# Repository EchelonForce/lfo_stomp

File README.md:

# Eurorack LFO Stomp

This is a PCB for a eurorack LFO based on the STOMPLFO chip from Electric Druid.

Full writeup here: https://www.robotdialogs.com/2022/09/eurorack-lfo-module-stomp-lfo.html

This work is licensed under a Creative Commons Attribution-NonCommercial-ShareAlike 4.0 International License. https://creativecommons.org/licenses/by-nc-sa/4.0/

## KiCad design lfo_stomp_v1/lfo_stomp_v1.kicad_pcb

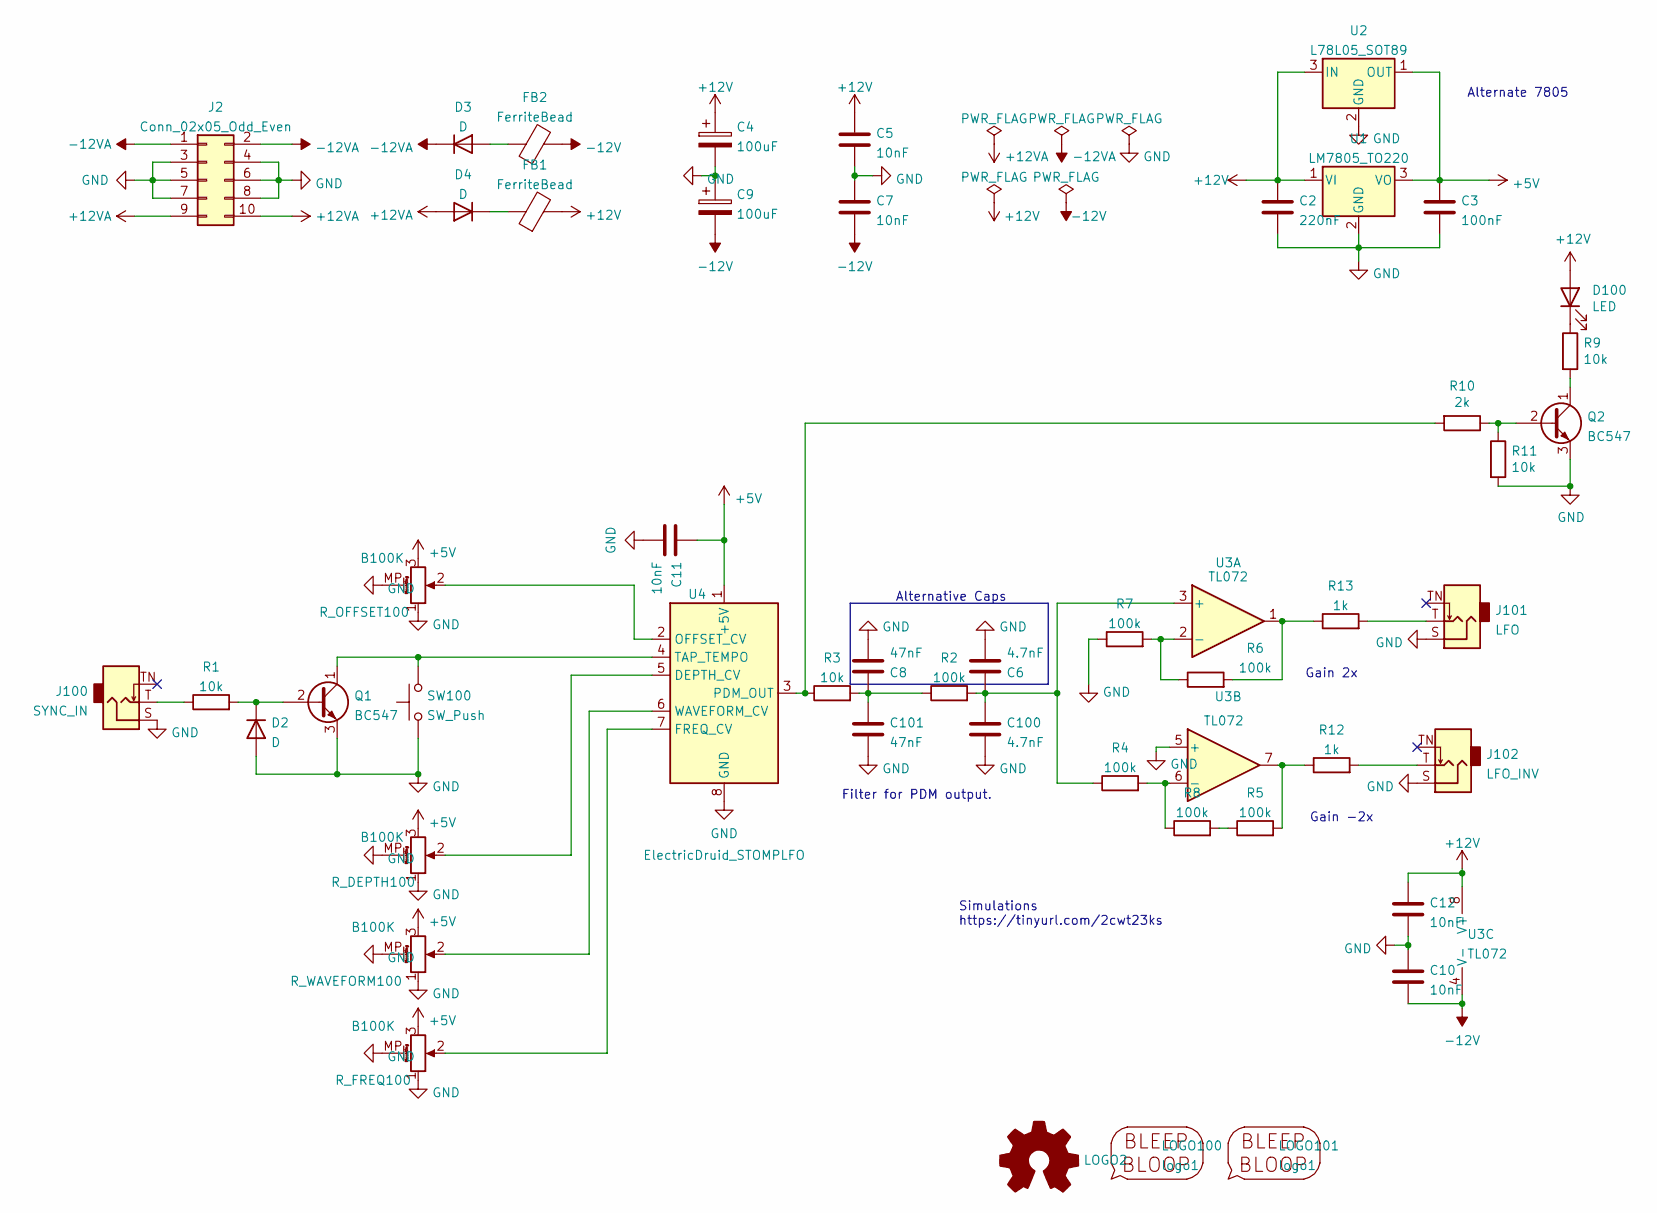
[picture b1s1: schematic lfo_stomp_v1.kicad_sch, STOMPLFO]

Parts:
C2: 220nF; C_1206_3216Metric_Pad1.33x1.80mm_HandSolder
C3: 100nF; C_1206_3216Metric_Pad1.33x1.80mm_HandSolder
C4, C9: 100uF; CP_Radial_D5.0mm_P2.50mm
C5, C7, C10, C11, C12: 10nF; C_1206_3216Metric_Pad1.33x1.80mm_HandSolder
C6: 4.7nF; C_1206_3216Metric_Pad1.33x1.80mm_HandSolder
C8: 47nF; C_1206_3216Metric_Pad1.33x1.80mm_HandSolder
C100: 4.7nF; C_Disc_D5.1mm_W3.2mm_P5.00mm
C101: 47nF; C_Disc_D5.1mm_W3.2mm_P5.00mm
D2, D3, D4: D; D_A-405_P7.62mm_Horizontal
D100: LED; LED_D3.0mm
FB1, FB2: FerriteBead; L_Axial_L5.3mm_D2.2mm_P2.54mm_Vertical_Vishay_IM-1
J2: Conn_02x05_Odd_Even; IDC-Header_2x05_P2.54mm_Vertical
J100: SYNC_IN; Jack_3.5mm_MJ-355W_and_PJ398SM_Vertical
J101: LFO; Jack_3.5mm_MJ-355W_and_PJ398SM_Vertical
J102: LFO_INV; Jack_3.5mm_MJ-355W_and_PJ398SM_Vertical
LOGO2: Logo_Open_Hardware_Small; OSHW-Symbol_6.7x6mm_SilkScreen
LOGO100: logo1; Logo1
LOGO101: logo1; Logo2
Q1, Q2: BC547; TO-92_Inline_Wide
R1, R3, R9, R11: 10k; R_1206_3216Metric_Pad1.30x1.75mm_HandSolder
R2, R4, R5, R6, R7, R8: 100k; R_1206_3216Metric_Pad1.30x1.75mm_HandSolder
R10: 2k; R_1206_3216Metric_Pad1.30x1.75mm_HandSolder
R12, R13: 1k; R_1206_3216Metric_Pad1.30x1.75mm_HandSolder
R_DEPTH100: B100K; Potentiometer_Alpha_RD901F-40-00D_Single_Vertical_w_3d
R_FREQ100: B100K; Potentiometer_Alpha_RD901F-40-00D_Single_Vertical_w_3d
R_OFFSET100: B100K; Potentiometer_Alpha_RD901F-40-00D_Single_Vertical_w_3d
R_WAVEFORM100: B100K; Potentiometer_Alpha_RD901F-40-00D_Single_Vertical_w_3d
SW100: SW_Push; SW_PS1024ALRED
U1: LM7805_TO220; TO-220-3_Vertical
U2: L78L05_SOT89; SOT-89-3
U3: TL072; DIP-8_W7.62mm_Socket_LongPads
U4: ElectricDruid_STOMPLFO; DIP-8_W7.62mm_Socket_LongPads

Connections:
+5V: C3.1, C11.1, R_DEPTH100.3, R_FREQ100.3, R_OFFSET100.3, R_WAVEFORM100.3, U1.3 (VO), U2.1 (OUT), U4.1 (+5V)
+12V: C2.1, C4.1, C5.1, C12.1, D100.2 (A), FB1.2, U1.1 (VI), U2.3 (IN), U3.8 (V+)
+12VA: D4.2 (A), J2.9, J2.10
-12V: C7.2, C9.2, C10.2, FB2.2, U3.4 (V-)
-12VA: D3.1 (K), J2.1, J2.2
GND: C2.2, C3.2, C4.2, C5.2, C6.2, C7.1, C8.2, C9.1, C10.1, C11.2, C12.2, C100.2, C101.2, D2.2 (A), J2.3, J2.4, J2.5, J2.6, J2.7, J2.8, J100.S, J101.S, J102.S, Q1.3 (E), Q2.3 (E), R7.1, R11.2, R_DEPTH100.1, R_DEPTH100.MP (MountPin), R_FREQ100.1, R_FREQ100.MP (MountPin), R_OFFSET100.1, R_OFFSET100.MP (MountPin), R_WAVEFORM100.1, R_WAVEFORM100.MP (MountPin), SW100.1, U1.2 (GND), U2.2 (GND), U3.5 (+), U4.8 (GND)
unnamed: C6.1, C100.1, R2.2, R4.1, U3.3 (+)
unnamed: C8.1, C101.1, R2.1, R3.2
unnamed: D2.1 (K), Q1.2 (B), R1.2
unnamed: D3.2 (A), FB2.1
unnamed: D4.1 (K), FB1.1
unnamed: D100.1 (K), R9.1
unnamed: J100.T, R1.1
unnamed: J101.T, R13.2
unnamed: J102.T, R12.2
unnamed: Q1.1 (C), SW100.2, U4.4 (TAP_TEMPO)
unnamed: R3.1, R10.2, U4.3 (PDM_OUT)
unnamed: R4.2, R8.1, U3.6 (-)
unnamed: R5.1, R8.2
unnamed: R6.1, R7.2, U3.2 (-)
unnamed: Q2.1 (C), R9.2
unnamed: Q2.2 (B), R10.1, R11.1
unnamed: R5.2, R12.1, U3.7
unnamed: R6.2, R13.1, U3.1
unnamed: R_DEPTH100.2, U4.5 (DEPTH_CV)
unnamed: R_FREQ100.2, U4.7 (FREQ_CV)
unnamed: R_OFFSET100.2, U4.2 (OFFSET_CV)
unnamed: R_WAVEFORM100.2, U4.6 (WAVEFORM_CV)

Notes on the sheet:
Filter for PDM output.
Gain 2x
Gain -2x
Simulations https://tinyurl.com/2cwt23ks
Alternate 7805
Alternative Caps

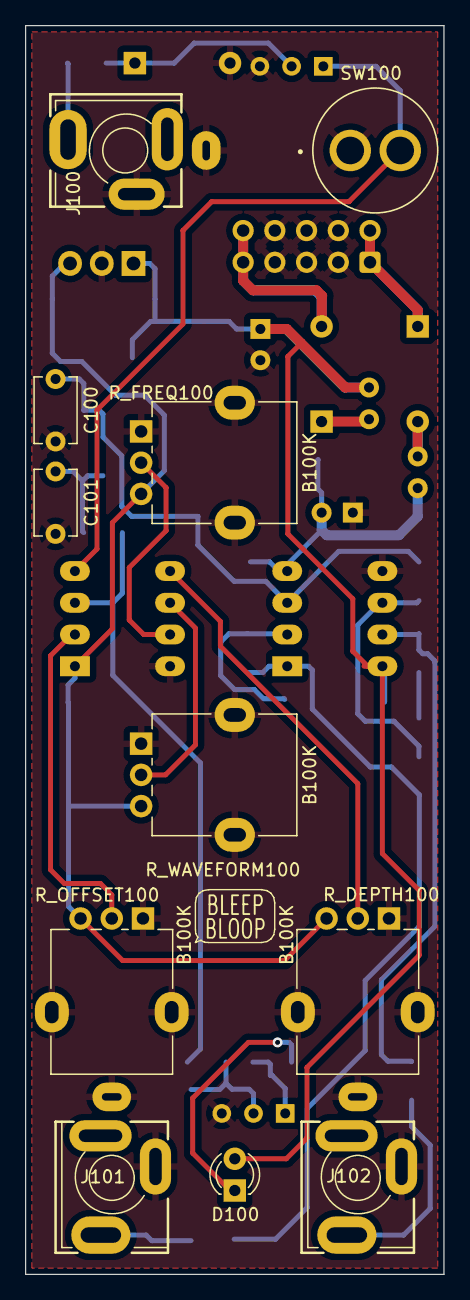
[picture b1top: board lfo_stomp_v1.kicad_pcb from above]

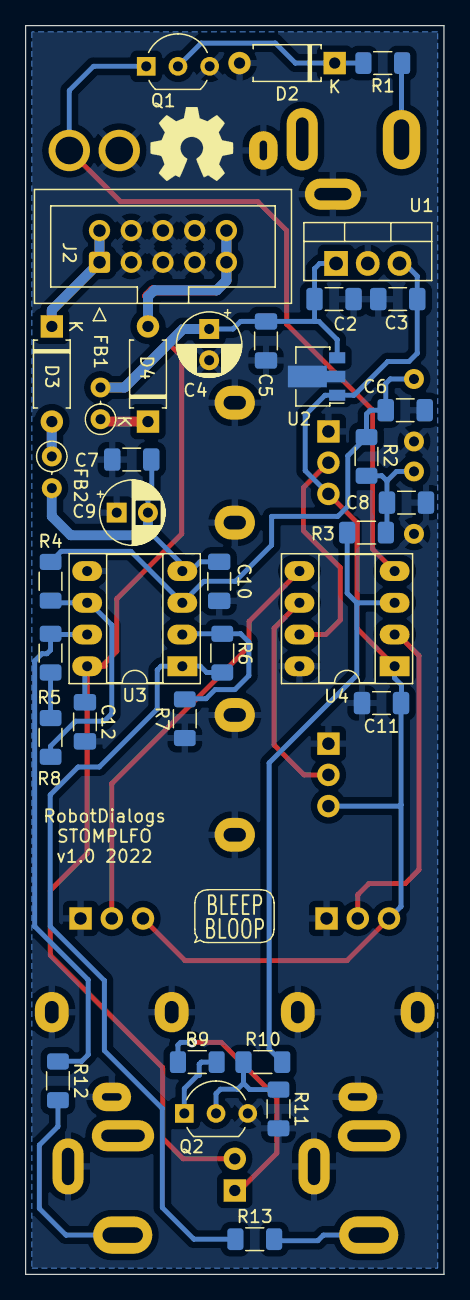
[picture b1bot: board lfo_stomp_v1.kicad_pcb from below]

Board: 2 copper layers, 33.5 x 100.0 mm, 50 parts (37 on the bottom side), 28 nets.

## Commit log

2022-06-25 Initial commit with .gitignore
2022-06-25 v1 before renaming references
2022-06-25 Geographic reannotate
2022-06-25 Page titles and fixed pot orientations
2022-07-07 Cleanup
2022-07-27 panelized v1
2022-07-27 v1 BOM and Notes.txt
2022-09-07 Front Panel v1 CAD
2022-09-07 Front Panel v1.1
    Moved engraving around
2022-09-07 Notes update and README
2022-09-07 Add schematic pdf
